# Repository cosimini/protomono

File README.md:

# Protomono

A prototype of a mono board ergo keyboard. This is mainly to test the layout, if I find it confortable, I will make a better version.
Also, I'm considering making use of all the space available to place some components I want to test, in particular I'd like to layout some microcontrollers.

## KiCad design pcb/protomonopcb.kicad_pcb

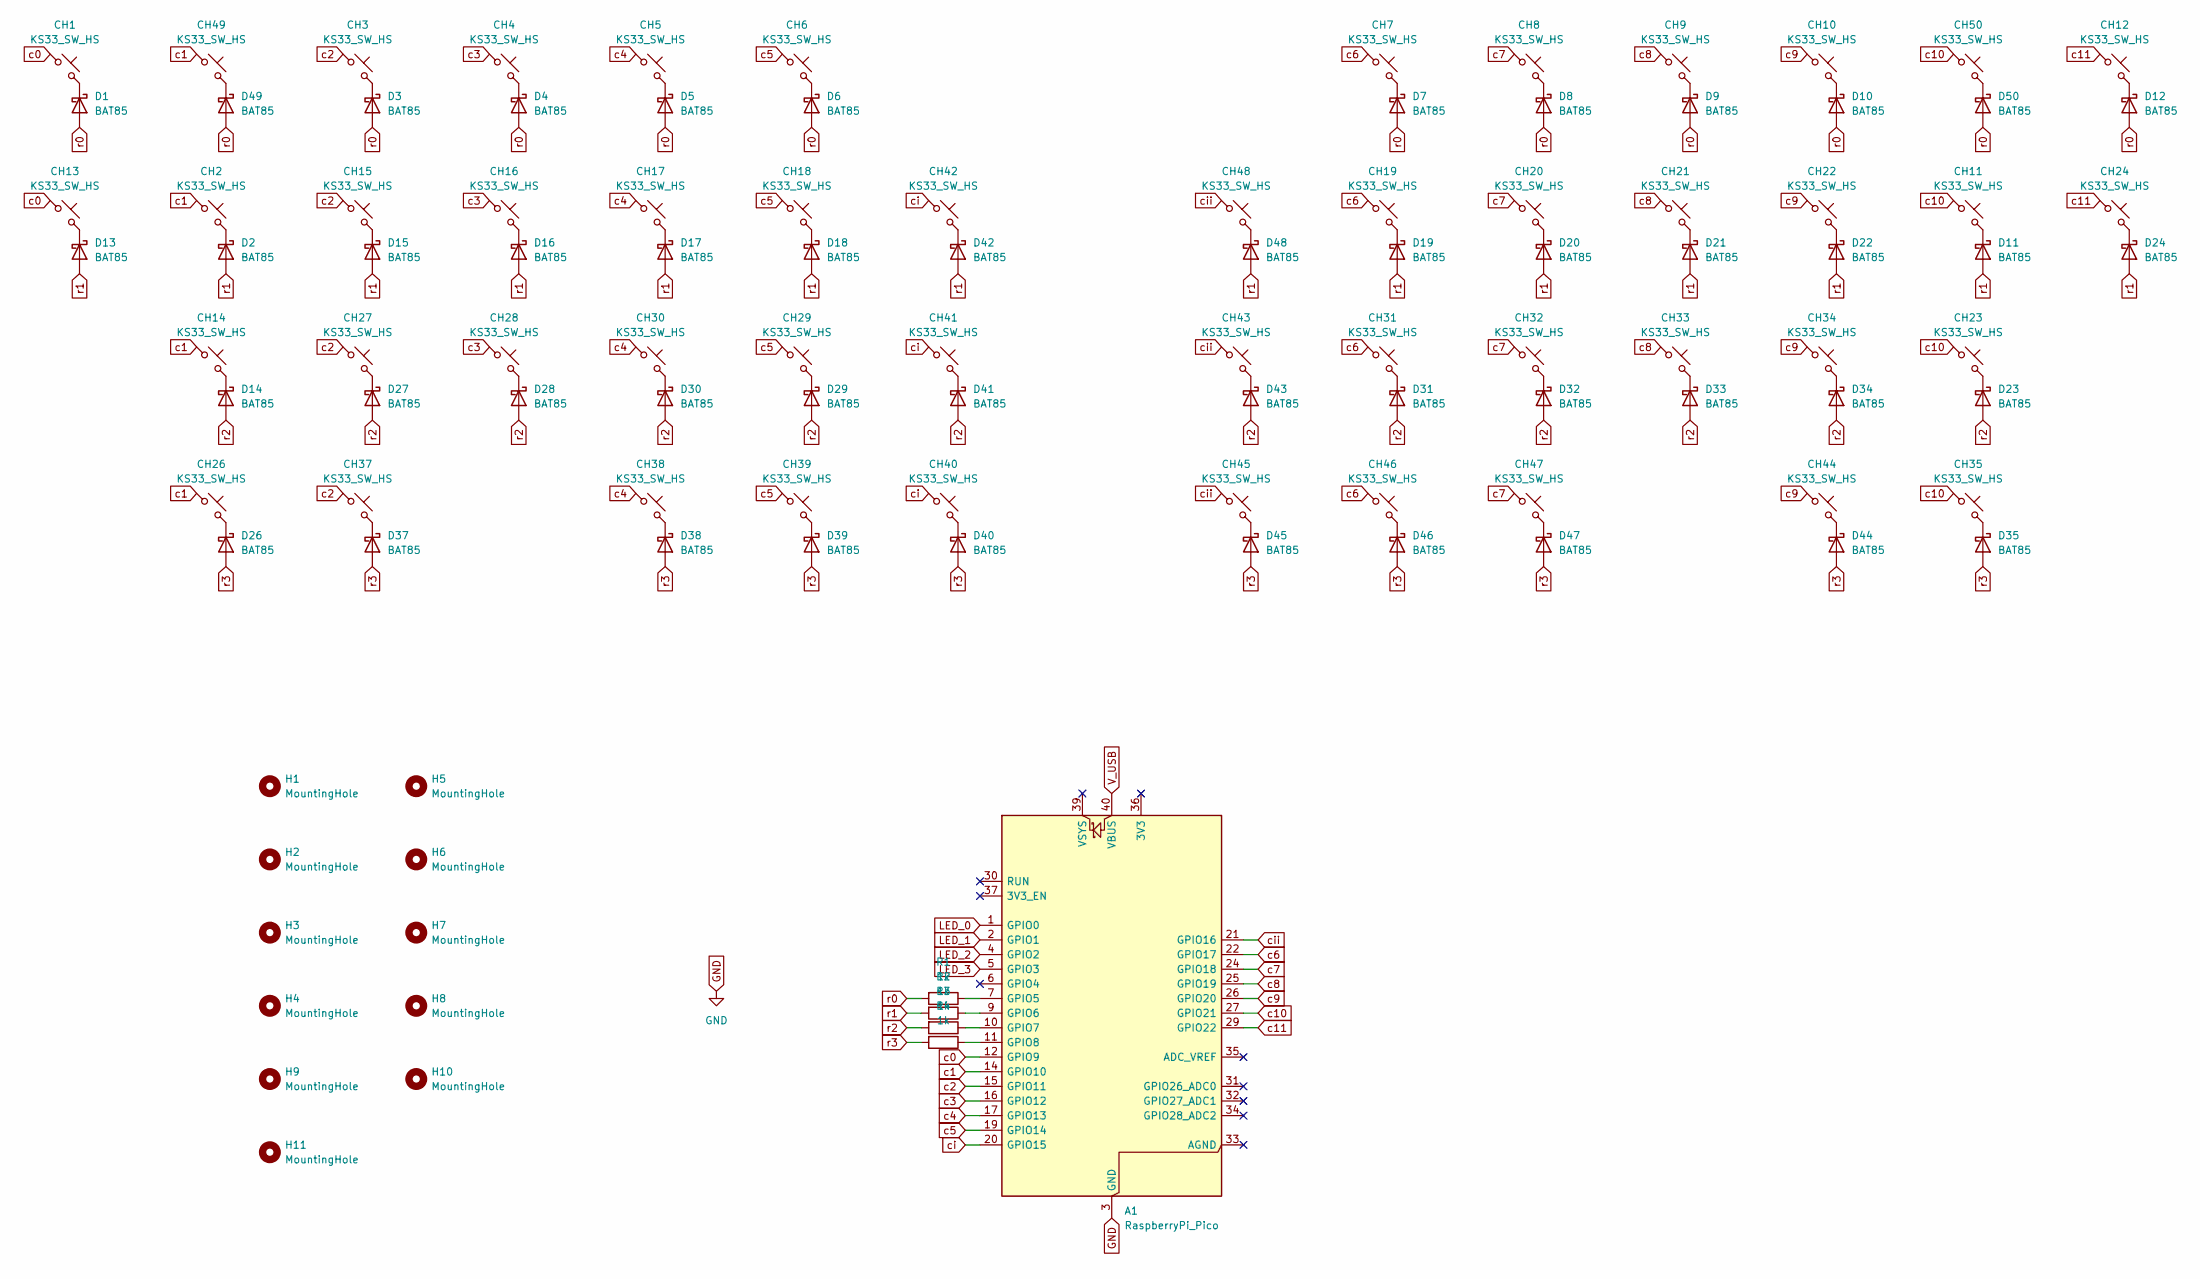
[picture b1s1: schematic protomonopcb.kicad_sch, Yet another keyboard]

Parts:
A1: RaspberryPi_Pico; RaspberryPi_Pico_Common_Unspecified
CH1, CH2, CH3, CH4, CH5, CH6, CH7, CH8, CH9, CH10, CH11, CH12, CH13, CH14, CH15, CH16, CH17, CH18, CH19, CH20, CH21, CH22, CH23, CH24, CH26, CH27, CH28, CH29, CH30, CH31, CH32, CH33, CH34, CH35, CH37, CH38, CH39, CH40, CH41, CH42, CH43, CH44, CH45, CH46, CH47, CH48, CH49, CH50: KS33_SW_HS; SW_KS33_HS_1u_18.5mm
D1, D2, D3, D4, D5, D6, D7, D8, D9, D10, D11, D12, D13, D14, D15, D16, D17, D18, D19, D20, D21, D22, D23, D24, D26, D27, D28, D29, D30, D31, D32, D33, D34, D35, D37, D38, D39, D40, D41, D42, D43, D44, D45, D46, D47, D48, D49, D50: BAT85; D_DO-35_SOD27_P7.62mm_Horizontal
H1, H2, H3, H4, H5, H6, H7, H8, H9, H10, H11: MountingHole; MountingHole_3.2mm_M3_Pad_Via
R1, R2, R3, R4: 1k; R_Axial_DIN0204_L3.6mm_D1.6mm_P7.62mm_Horizontal

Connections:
GND: A1.3 (GND), A1.8 (GND), A1.13 (GND), A1.18 (GND), A1.23 (GND), A1.28 (GND), A1.38 (GND)
LED_0: A1.1 (GPIO0)
LED_1: A1.2 (GPIO1)
LED_2: A1.4 (GPIO2)
LED_3: A1.5 (GPIO3)
unnamed: A1.7 (GPIO5), R1.1
unnamed: A1.9 (GPIO6), R2.1
unnamed: A1.10 (GPIO7), R3.1
unnamed: A1.11 (GPIO8), R4.1
unnamed: CH1.2, D1.1 (K)
unnamed: CH2.2, D2.1 (K)
unnamed: CH3.2, D3.1 (K)
unnamed: CH4.2, D4.1 (K)
unnamed: CH5.2, D5.1 (K)
unnamed: CH6.2, D6.1 (K)
unnamed: CH7.2, D7.1 (K)
unnamed: CH8.2, D8.1 (K)
unnamed: CH9.2, D9.1 (K)
unnamed: CH10.2, D10.1 (K)
unnamed: CH11.2, D11.1 (K)
unnamed: CH12.2, D12.1 (K)
unnamed: CH13.2, D13.1 (K)
unnamed: CH14.2, D14.1 (K)
unnamed: CH15.2, D15.1 (K)
unnamed: CH16.2, D16.1 (K)
unnamed: CH17.2, D17.1 (K)
unnamed: CH18.2, D18.1 (K)
unnamed: CH19.2, D19.1 (K)
unnamed: CH20.2, D20.1 (K)
unnamed: CH21.2, D21.1 (K)
unnamed: CH22.2, D22.1 (K)
unnamed: CH23.2, D23.1 (K)
unnamed: CH24.2, D24.1 (K)
unnamed: CH26.2, D26.1 (K)
unnamed: CH27.2, D27.1 (K)
unnamed: CH28.2, D28.1 (K)
unnamed: CH29.2, D29.1 (K)
unnamed: CH30.2, D30.1 (K)
unnamed: CH31.2, D31.1 (K)
unnamed: CH32.2, D32.1 (K)
unnamed: CH33.2, D33.1 (K)
unnamed: CH34.2, D34.1 (K)
unnamed: CH35.2, D35.1 (K)
unnamed: CH37.2, D37.1 (K)
unnamed: CH38.2, D38.1 (K)
unnamed: CH39.2, D39.1 (K)
unnamed: CH40.2, D40.1 (K)
unnamed: CH41.2, D41.1 (K)
unnamed: CH42.2, D42.1 (K)
unnamed: CH43.2, D43.1 (K)
unnamed: CH44.2, D44.1 (K)
unnamed: CH45.2, D45.1 (K)
unnamed: CH46.2, D46.1 (K)
unnamed: CH47.2, D47.1 (K)
unnamed: CH48.2, D48.1 (K)
unnamed: CH49.2, D49.1 (K)
unnamed: CH50.2, D50.1 (K)
V_USB: A1.40 (VBUS)
c0: A1.12 (GPIO9), CH1.1, CH13.1
c1: A1.14 (GPIO10), CH2.1, CH14.1, CH26.1, CH49.1
c2: A1.15 (GPIO11), CH3.1, CH15.1, CH27.1, CH37.1
c3: A1.16 (GPIO12), CH4.1, CH16.1, CH28.1
c4: A1.17 (GPIO13), CH5.1, CH17.1, CH30.1, CH38.1
c5: A1.19 (GPIO14), CH6.1, CH18.1, CH29.1, CH39.1
c6: A1.22 (GPIO17), CH7.1, CH19.1, CH31.1, CH46.1
c7: A1.24 (GPIO18), CH8.1, CH20.1, CH32.1, CH47.1
c8: A1.25 (GPIO19), CH9.1, CH21.1, CH33.1
c9: A1.26 (GPIO20), CH10.1, CH22.1, CH34.1, CH44.1
c10: A1.27 (GPIO21), CH11.1, CH23.1, CH35.1, CH50.1
c11: A1.29 (GPIO22), CH12.1, CH24.1
ci: A1.20 (GPIO15), CH40.1, CH41.1, CH42.1
cii: A1.21 (GPIO16), CH43.1, CH45.1, CH48.1
r0: D1.2 (A), D3.2 (A), D4.2 (A), D5.2 (A), D6.2 (A), D7.2 (A), D8.2 (A), D9.2 (A), D10.2 (A), D12.2 (A), D49.2 (A), D50.2 (A), R1.2
r1: D2.2 (A), D11.2 (A), D13.2 (A), D15.2 (A), D16.2 (A), D17.2 (A), D18.2 (A), D19.2 (A), D20.2 (A), D21.2 (A), D22.2 (A), D24.2 (A), D42.2 (A), D48.2 (A), R2.2
r2: D14.2 (A), D23.2 (A), D27.2 (A), D28.2 (A), D29.2 (A), D30.2 (A), D31.2 (A), D32.2 (A), D33.2 (A), D34.2 (A), D41.2 (A), D43.2 (A), R3.2
r3: D26.2 (A), D35.2 (A), D37.2 (A), D38.2 (A), D39.2 (A), D40.2 (A), D44.2 (A), D45.2 (A), D46.2 (A), D47.2 (A), R4.2

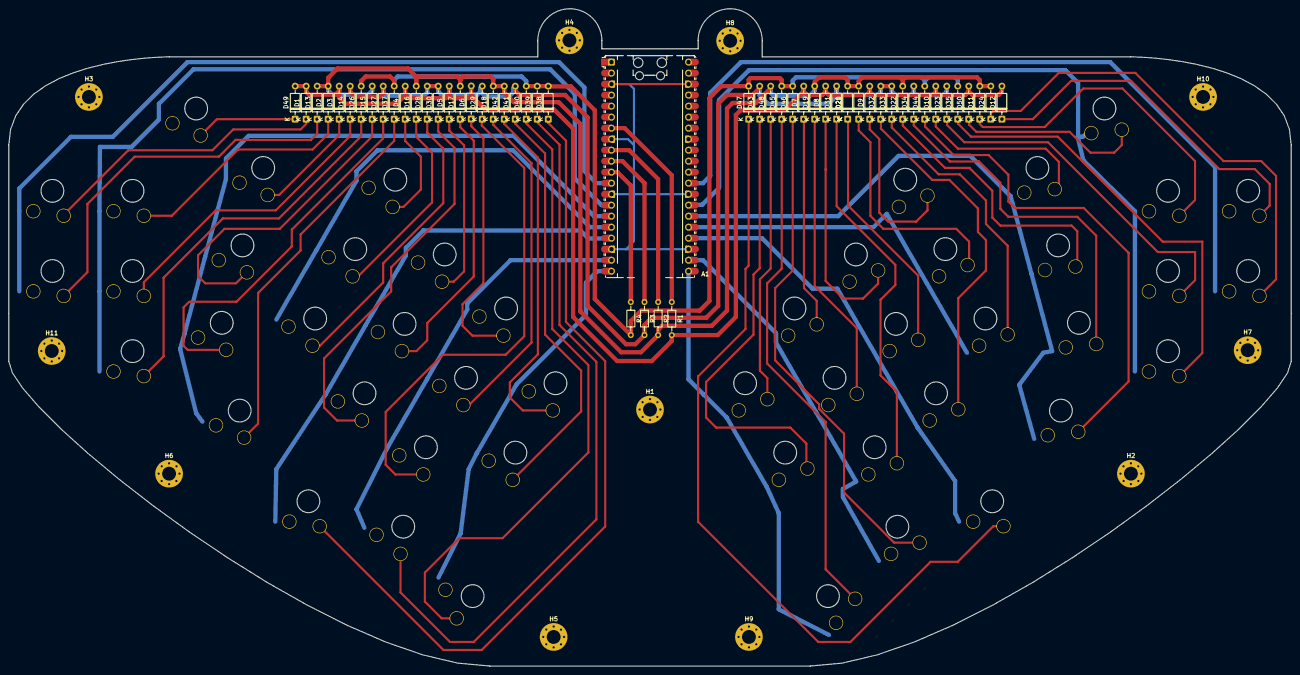
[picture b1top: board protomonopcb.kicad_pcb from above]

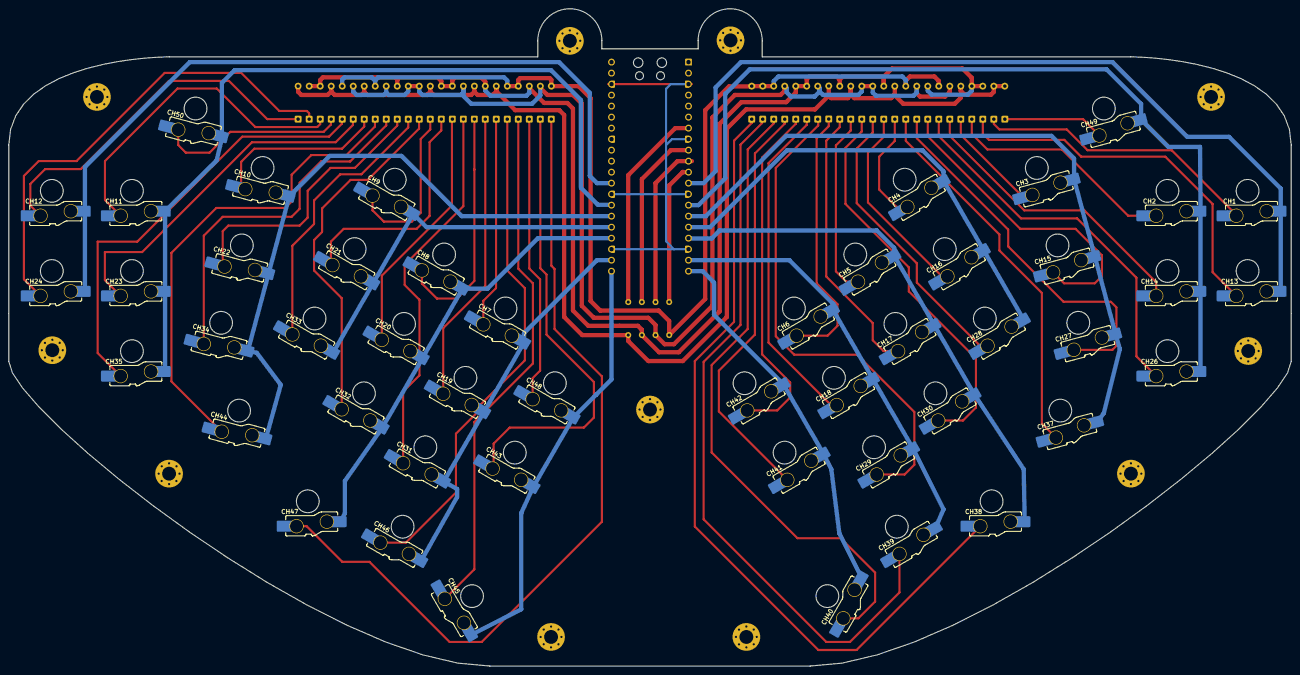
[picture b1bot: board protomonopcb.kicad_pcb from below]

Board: 2 copper layers, 296.0 x 151.7 mm, 112 parts (48 on the bottom side), 71 nets.

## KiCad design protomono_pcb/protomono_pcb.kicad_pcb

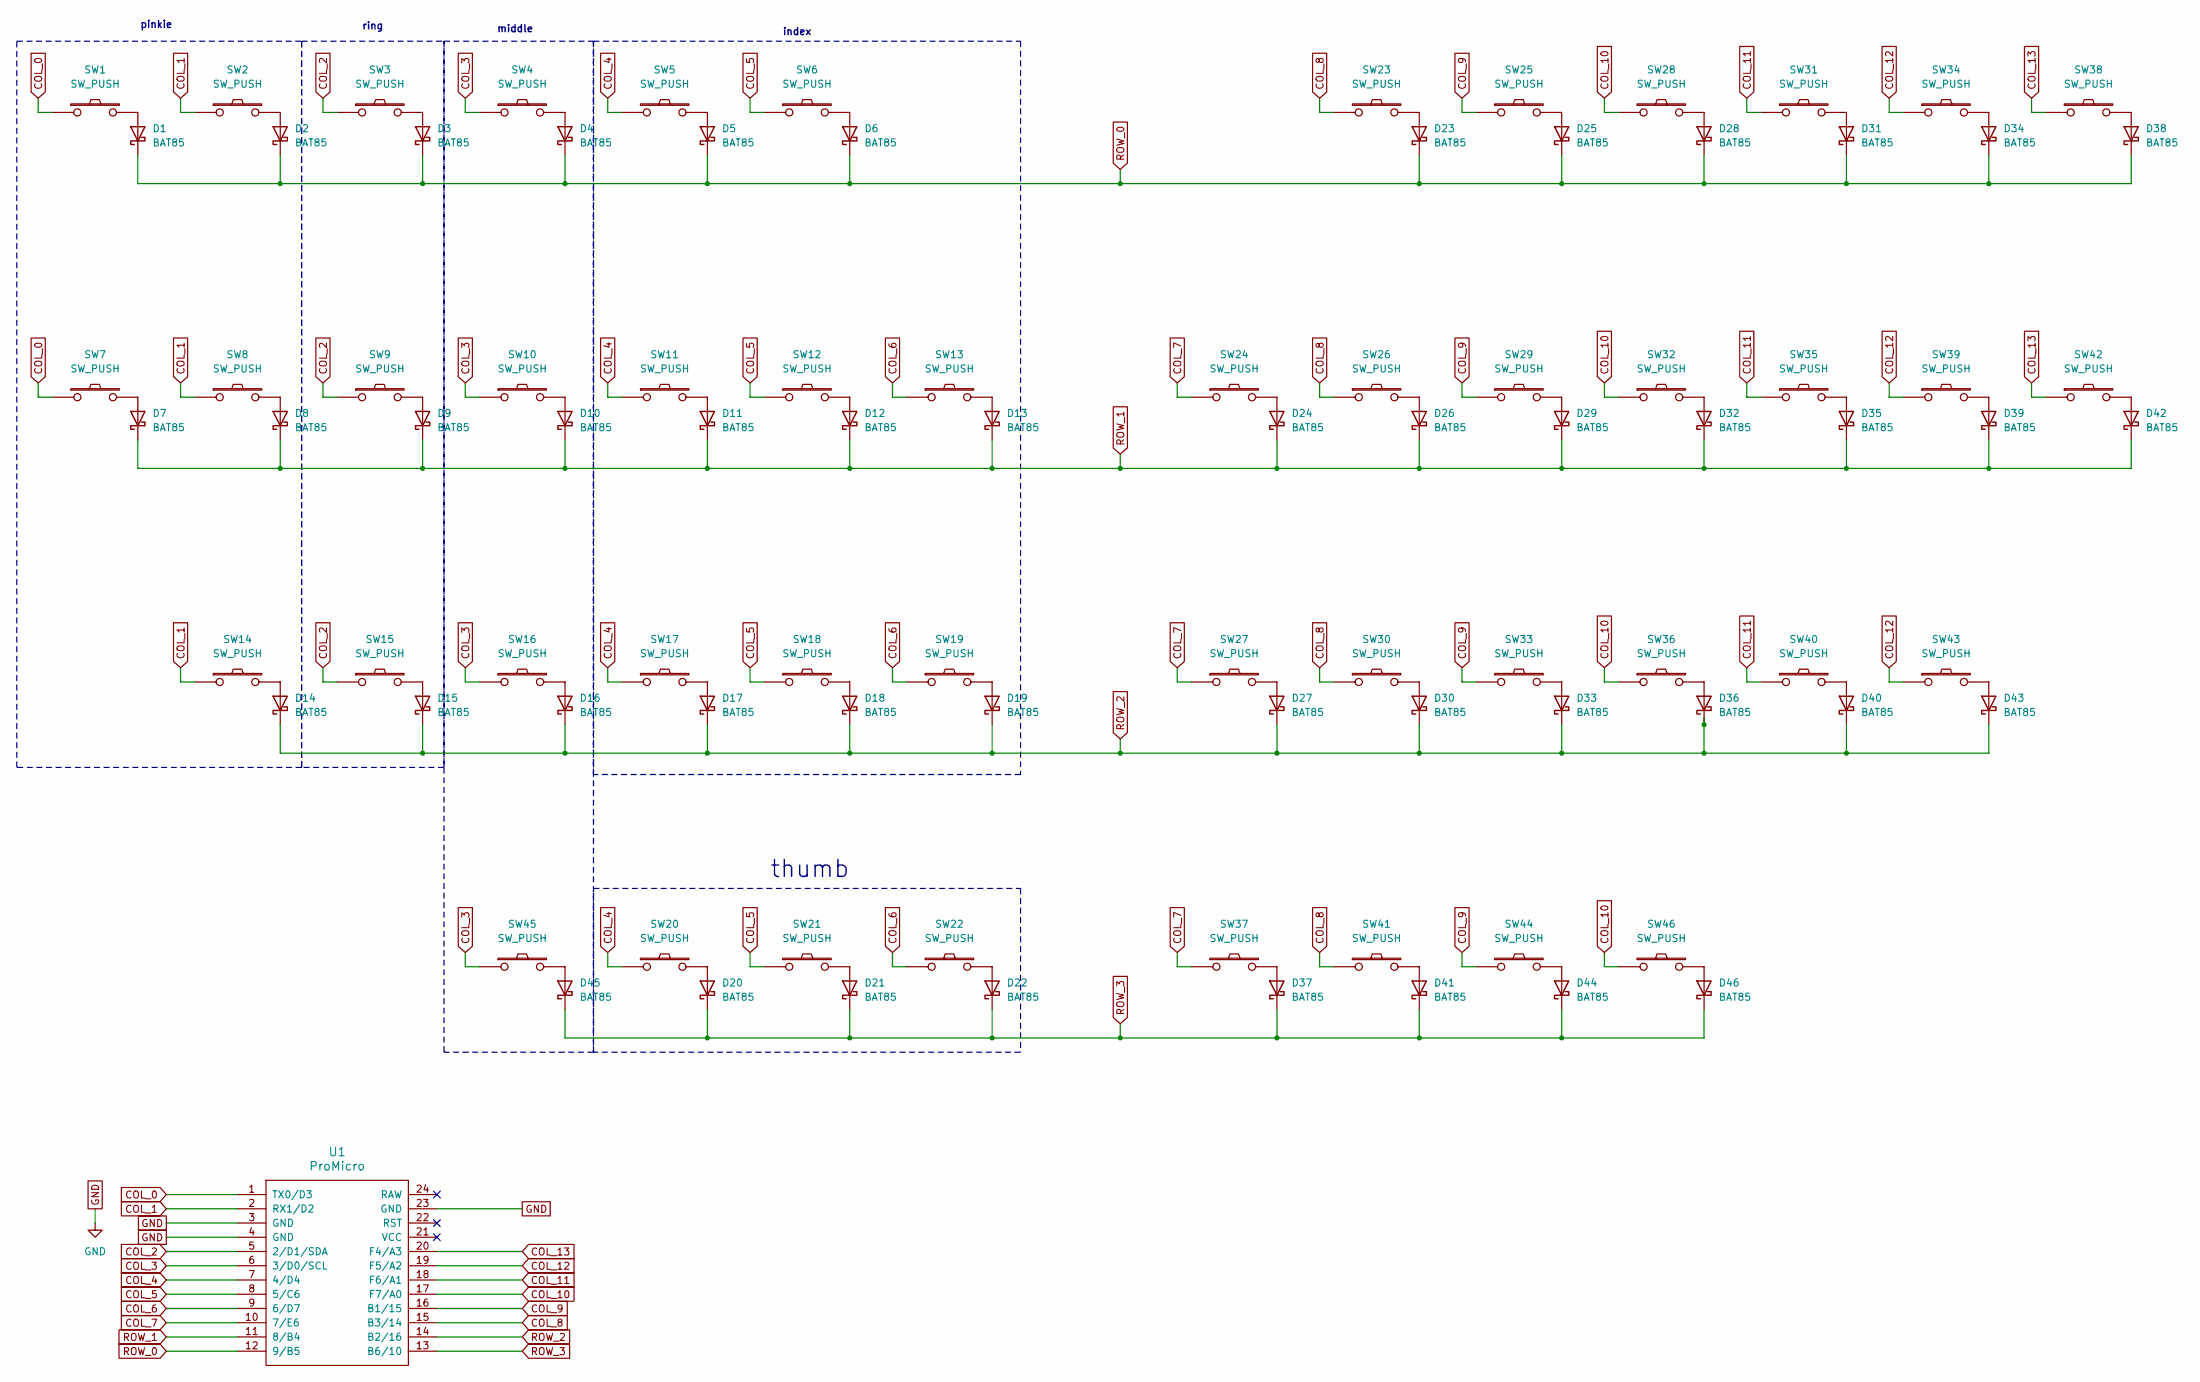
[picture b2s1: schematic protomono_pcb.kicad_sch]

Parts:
D1, D2, D3, D4, D5, D6, D7, D8, D9, D10, D11, D12, D13, D14, D15, D16, D17, D18, D19, D20, D21, D22, D23, D24, D25, D26, D27, D28, D29, D30, D31, D32, D33, D34, D35, D36, D37, D38, D39, D40, D41, D42, D43, D44, D45, D46: BAT85; D_DO-35_SOD27_P7.62mm_Horizontal
SW1, SW2, SW3, SW4, SW5, SW6, SW7, SW8, SW9, SW10, SW11, SW12, SW13, SW14, SW15, SW16, SW17, SW18, SW19, SW20, SW21, SW22, SW23, SW24, SW25, SW26, SW27, SW28, SW29, SW30, SW31, SW32, SW33, SW34, SW35, SW36, SW37, SW38, SW39, SW40, SW41, SW42, SW43, SW44, SW45, SW46: SW_PUSH; keyswitch_gateron_low_profile_hotswap_1u
U1: ProMicro

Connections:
COL_0: SW1.1, SW7.1, U1.1 (TX0/D3)
COL_1: SW2.1, SW8.1, SW14.1, U1.2 (RX1/D2)
COL_2: SW3.1, SW9.1, SW15.1, U1.5 (2/D1/SDA)
COL_3: SW4.1, SW10.1, SW16.1, SW45.1, U1.6 (3/D0/SCL)
COL_4: SW5.1, SW11.1, SW17.1, SW20.1, U1.7 (4/D4)
COL_5: SW6.1, SW12.1, SW18.1, SW21.1, U1.8 (5/C6)
COL_6: SW13.1, SW19.1, SW22.1, U1.9 (6/D7)
COL_7: SW24.1, SW27.1, SW37.1, U1.10 (7/E6)
COL_8: SW23.1, SW26.1, SW30.1, SW41.1, U1.15 (B3/14)
COL_9: SW25.1, SW29.1, SW33.1, SW44.1, U1.16 (B1/15)
COL_10: SW28.1, SW32.1, SW36.1, SW46.1, U1.17 (F7/A0)
COL_11: SW31.1, SW35.1, SW40.1, U1.18 (F6/A1)
COL_12: SW34.1, SW39.1, SW43.1, U1.19 (F5/A2)
COL_13: SW38.1, SW42.1, U1.20 (F4/A3)
GND: U1.3 (GND), U1.4 (GND), U1.23 (GND)
unnamed: D1.2 (A), SW1.2
unnamed: D2.2 (A), SW2.2
unnamed: D3.2 (A), SW3.2
unnamed: D4.2 (A), SW4.2
unnamed: D5.2 (A), SW5.2
unnamed: D6.2 (A), SW6.2
unnamed: D7.2 (A), SW7.2
unnamed: D8.2 (A), SW8.2
unnamed: D9.2 (A), SW9.2
unnamed: D10.2 (A), SW10.2
unnamed: D11.2 (A), SW11.2
unnamed: D12.2 (A), SW12.2
unnamed: D13.2 (A), SW13.2
unnamed: D14.2 (A), SW14.2
unnamed: D15.2 (A), SW15.2
unnamed: D16.2 (A), SW16.2
unnamed: D17.2 (A), SW17.2
unnamed: D18.2 (A), SW18.2
unnamed: D19.2 (A), SW19.2
unnamed: D20.2 (A), SW20.2
unnamed: D21.2 (A), SW21.2
unnamed: D22.2 (A), SW22.2
unnamed: D23.2 (A), SW23.2
unnamed: D24.2 (A), SW24.2
unnamed: D25.2 (A), SW25.2
unnamed: D26.2 (A), SW26.2
unnamed: D27.2 (A), SW27.2
unnamed: D28.2 (A), SW28.2
unnamed: D29.2 (A), SW29.2
unnamed: D30.2 (A), SW30.2
unnamed: D31.2 (A), SW31.2
unnamed: D32.2 (A), SW32.2
unnamed: D33.2 (A), SW33.2
unnamed: D34.2 (A), SW34.2
unnamed: D35.2 (A), SW35.2
unnamed: D36.2 (A), SW36.2
unnamed: D37.2 (A), SW37.2
unnamed: D38.2 (A), SW38.2
unnamed: D39.2 (A), SW39.2
unnamed: D40.2 (A), SW40.2
unnamed: D41.2 (A), SW41.2
unnamed: D42.2 (A), SW42.2
unnamed: D43.2 (A), SW43.2
unnamed: D44.2 (A), SW44.2
unnamed: D45.2 (A), SW45.2
unnamed: D46.2 (A), SW46.2
ROW_0: D1.1 (K), D2.1 (K), D3.1 (K), D4.1 (K), D5.1 (K), D6.1 (K), D23.1 (K), D25.1 (K), D28.1 (K), D31.1 (K), D34.1 (K), D38.1 (K), U1.12 (9/B5)
ROW_1: D7.1 (K), D8.1 (K), D9.1 (K), D10.1 (K), D11.1 (K), D12.1 (K), D13.1 (K), D24.1 (K), D26.1 (K), D29.1 (K), D32.1 (K), D35.1 (K), D39.1 (K), D42.1 (K), U1.11 (8/B4)
ROW_2: D14.1 (K), D15.1 (K), D16.1 (K), D17.1 (K), D18.1 (K), D19.1 (K), D27.1 (K), D30.1 (K), D33.1 (K), D36.1 (K), D40.1 (K), D43.1 (K), U1.14 (B2/16)
ROW_3: D20.1 (K), D21.1 (K), D22.1 (K), D37.1 (K), D41.1 (K), D44.1 (K), D45.1 (K), D46.1 (K), U1.13 (B6/10)

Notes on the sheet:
ring
pinkie
middle
index
thumb

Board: 2 copper layers, 93 parts (0 on the bottom side), 65 nets, no tracks yet.

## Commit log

2025-03-30 Add schematic
2025-03-30 Add a keymap/layout image
2025-03-30 Add readme.md
2025-04-07 Start laying the PCB down
2025-06-15 Use RP2040, remove one index key
2025-08-08 Been a while, changed quite a lot of stuff
    Noone carer, really
2025-10-19 Just another periodic push
2025-10-26 Bottom PCB completed
2025-10-26 Create plate
